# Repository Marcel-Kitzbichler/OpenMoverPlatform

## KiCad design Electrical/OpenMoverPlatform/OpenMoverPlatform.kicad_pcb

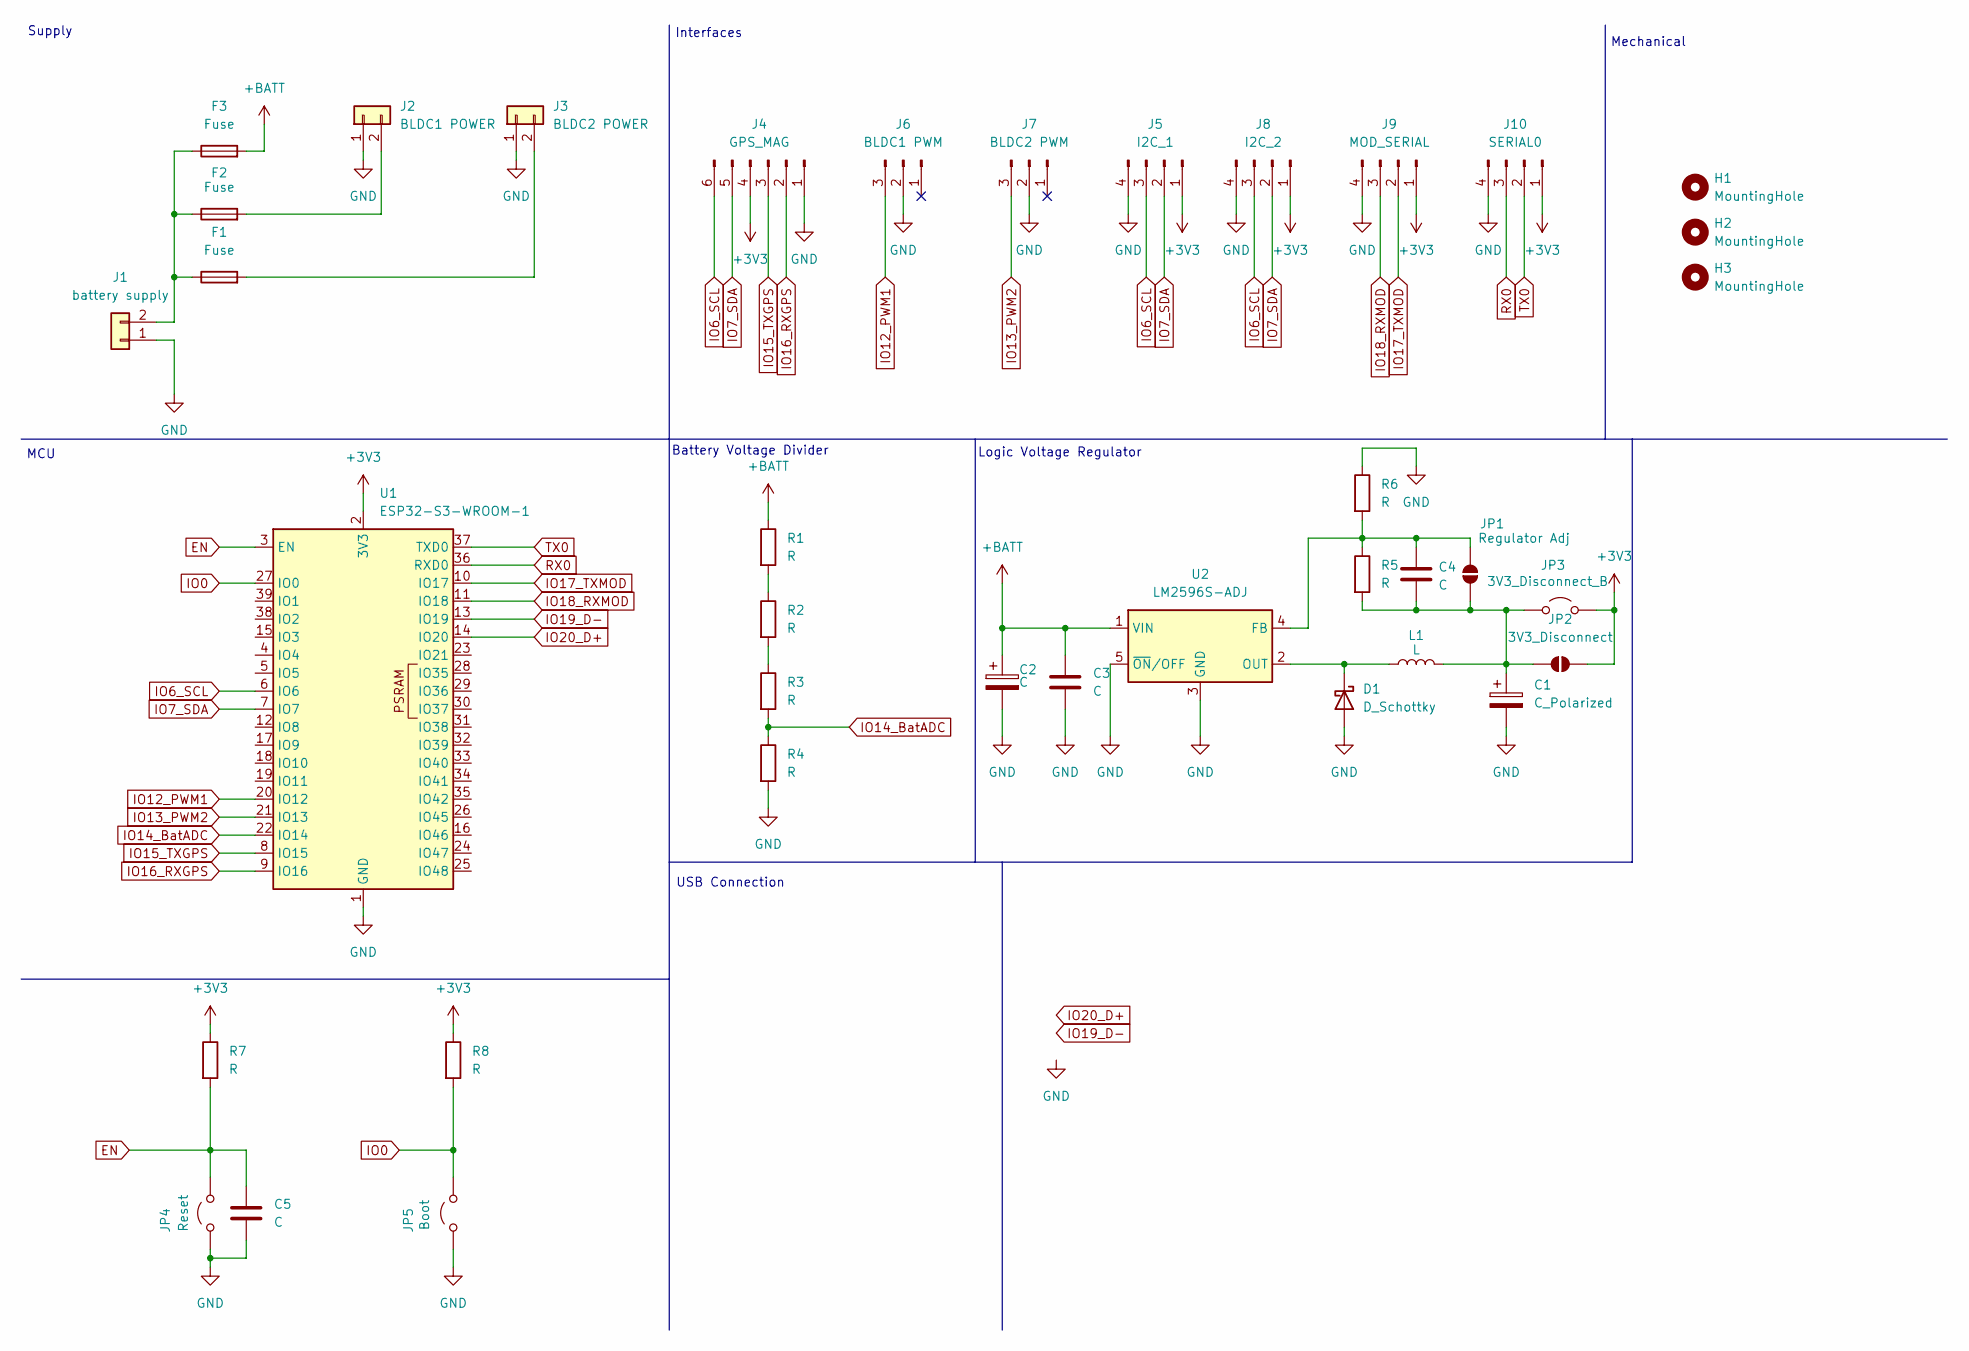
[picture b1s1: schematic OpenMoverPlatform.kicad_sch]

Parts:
C1: C_Polarized; CP_Elec_8x10.5
C2: C; CP_Elec_8x10.5
C3, C4, C5: C; C_1210_3225Metric_Pad1.33x2.70mm_HandSolder
D1: D_Schottky; D_SMA-SMB_Universal_Handsoldering
F1, F2, F3: Fuse; Fuseholder_Blade_Mini_Keystone_3568
H1, H2, H3: MountingHole; MountingHole_3.2mm_M3
J1: battery supply; AMASS_XT60-M_1x02_P7.20mm_Vertical
J2: BLDC1 POWER; AMASS_XT60-F_1x02_P7.20mm_Vertical
J3: BLDC2 POWER; AMASS_XT60-F_1x02_P7.20mm_Vertical
J4: GPS_MAG; PinHeader_1x06_P2.54mm_Vertical
J5: I2C_1; PinHeader_1x04_P2.54mm_Vertical
J6: BLDC1 PWM; PinHeader_1x03_P2.54mm_Vertical
J7: BLDC2 PWM; PinHeader_1x03_P2.54mm_Vertical
J8: I2C_2; PinHeader_1x04_P2.54mm_Vertical
J9: MOD_SERIAL; PinHeader_1x04_P2.54mm_Vertical
J10: SERIAL0; PinHeader_1x04_P2.54mm_Vertical
JP1: Regulator Adj; SolderJumper-2_P1.3mm_Open_TrianglePad1.0x1.5mm
JP2: 3V3_Disconnect; SolderJumper-2_P1.3mm_Open_TrianglePad1.0x1.5mm
JP3: 3V3_Disconnect_B; PinHeader_2x01_P2.54mm_Vertical
JP4: Reset; PinHeader_2x01_P2.54mm_Vertical
JP5: Boot; PinHeader_2x01_P2.54mm_Vertical
L1: L; L_Bourns_SRR1260
R1, R2, R3, R4, R5, R6, R7, R8: R; R_1206_3216Metric_Pad1.30x1.75mm_HandSolder
U1: ESP32-S3-WROOM-1
U2: LM2596S-ADJ; TO-263-5_TabPin3

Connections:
+3V3: J4.4, J5.1, J8.1, J9.1, J10.1, JP2.2 (B), JP3.2 (B), R7.1, R8.1, U1.2 (3V3); also elsewhere on the board
+BATT: C2.1, C3.1, F3.2, R1.1, U2.1 (VIN)
EN: C5.1, JP4.2 (B), R7.2, U1.3 (EN)
GND: C1.2, C2.2, C3.2, C5.2, D1.2 (A), J1.1, J2.1, J3.1, J4.1, J5.4, J6.2, J7.2, J8.4, J9.4, J10.4, JP4.1 (A), JP5.1 (A), R4.2, R6.1, U1.1 (GND), U1.40 (GND), U1.41 (GND), U2.3 (GND), U2.5 (~ON/OFF); also elsewhere on the board
IO0: JP5.2 (B), R8.2, U1.27 (IO0)
IO6_SCL: J4.6, J5.3, J8.3, U1.6 (IO6)
IO7_SDA: J4.5, J5.2, J8.2, U1.7 (IO7)
IO12_PWM1: J6.3, U1.20 (IO12)
IO13_PWM2: J7.3, U1.21 (IO13)
IO14_BatADC: R3.2, R4.1, U1.22 (IO14)
IO15_TXGPS: J4.3, U1.8 (IO15)
IO16_RXGPS: J4.2, U1.9 (IO16)
IO17_TXMOD: J9.2, U1.10 (IO17)
IO18_RXMOD: J9.3, U1.11 (IO18)
IO19_D-: U1.13 (IO19); also elsewhere on the board
IO20_D+: U1.14 (IO20); also elsewhere on the board
unnamed: D1.1 (K), L1.1, U2.2 (OUT)
unnamed: F1.1, F2.1, F3.1, J1.2
unnamed: F2.2, J2.2
unnamed: F1.2, J3.2
unnamed: C1.1, C4.2, JP1.1 (A), JP2.1 (A), JP3.1 (A), L1.2, R5.2
unnamed: C4.1, JP1.2 (B), R5.1, R6.2, U2.4 (FB)
unnamed: R1.2, R2.1
unnamed: R2.2, R3.1
RX0: J10.3, U1.36 (RXD0)
TX0: J10.2, U1.37 (TXD0)

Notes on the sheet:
Supply
Battery Voltage Divider
USB Connection
Mechanical
MCU
Logic Voltage Regulator
Interfaces

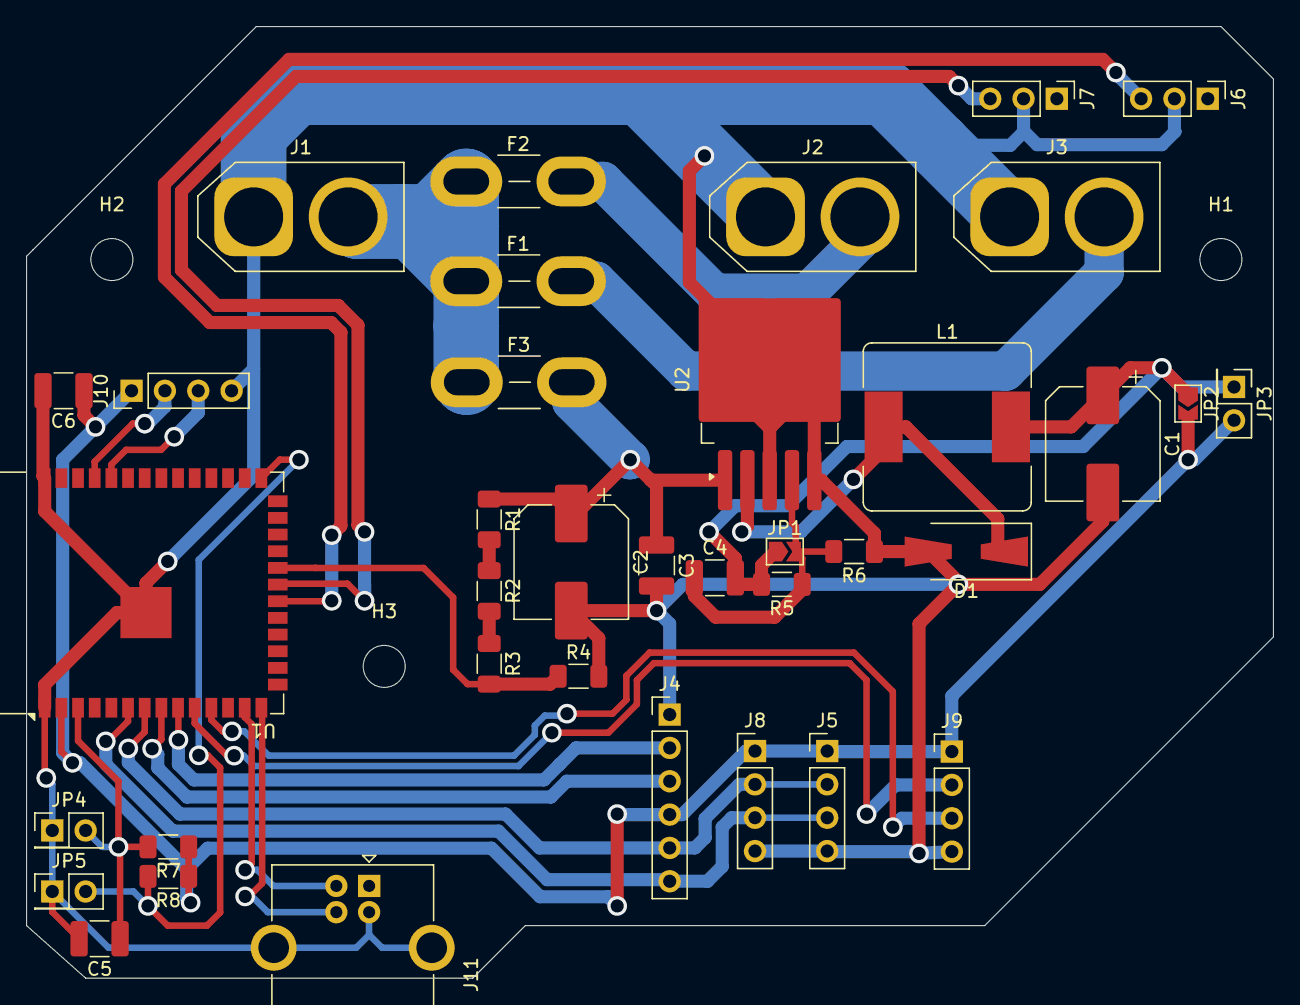
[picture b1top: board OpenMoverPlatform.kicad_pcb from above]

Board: 2 copper layers, 95.0 x 72.5 mm, 40 parts (0 on the bottom side), 26 nets.

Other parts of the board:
C6: C; C_1210_3225Metric_Pad1.33x2.70mm_HandSolder
J11: USB_B; USB_B_OST_USB-B1HSxx_Horizontal

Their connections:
+3V3: C6.1; also elsewhere on the board
GND: C6.2, J11.4 (GND), J11.5 (Shield); also elsewhere on the board
IO19_D-: J11.2 (D-); also elsewhere on the board
IO20_D+: J11.3 (D+); also elsewhere on the board

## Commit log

2024-11-12 added kicad project
2024-11-12 created platformcode
2024-11-12 KiCad save
2024-11-14 Rough sketch of chassis
    Not really to scale
2024-11-14 added DRIVEUNIT_V1
2024-11-15 update meshes
2024-11-15 updated motor mount
2024-11-21 added v2 driveunit
2024-11-29 swx update
2024-11-29 create platform io project
2024-12-06 Platform basic communication
2024-12-06 added coordinate parsing
2024-12-09 platfom update
2024-12-10 code update
2024-12-10 Passing data to WP manager
2024-12-12 added helper
2024-12-12 rearranged main
2024-12-12 added elif tree
2024-12-12 added example data
2024-12-12 added motor instance checking
2024-12-13 added multiple files to bot helper
2024-12-13 Changed intent numbering
2025-01-16 chain
    Added added chain design from filzer and set it to the correct length
2025-01-20 worked on coordinate storage
2025-01-20 added kml parser
2025-01-20 added coordinate transmission to helper
2025-01-20 added kml sample
2025-01-21 fixed PWM
2025-01-22 pwmUpdate
2025-01-22 updated deprecated json datatypes
2025-01-27 made usecPWM const
2025-01-27 added gps config
2025-01-28 removed debug messages
2025-01-28 added gps debug
2025-02-27 swxUpdate
2025-04-15 added bluetooth serial
2025-04-16 added direct serial control
2025-04-16 added Battery Reading Intent 6
2025-04-16 updated serial Timing and fixed correct decimal
2025-04-22 added motor set
2025-04-23 updated parsekml
2025-04-24 better gps
2025-04-24 update emerg
2025-04-30 added goto
2025-05-01 goto with compass
2025-05-02 updated bot helper
2025-05-06 Rim to WheelHolder
    Added a chain guide rail to make sure the chain doesn't slip off.
2025-05-08 added WP Manager and compass calibration routines
2025-05-08 updated bot helper desktop application
2025-05-08 added preferences with mag not yet implemented and intent 10
2025-05-10 Connector tolerance
    Updated connector tolerances to improve fit.
2025-05-12 corrected data type saved by preferences
2025-05-13 added nonlinear stearing curve
2025-05-13 added setpoints to motorset
2025-05-13 added setpoint to status
2025-05-14 control pcb v1
2025-05-16 ki cad pcb update
2025-05-16 added esp32s3 environment
2025-05-18 updated pcb to use esp32 s3 wroom 1
2025-05-29 working com on esp devboard, untested hardware peripherals
2025-05-29 add to last commit
2025-05-30 BLE Serial end detection
2025-05-30 updated to new ledc api
2025-10-23 update 2025
2025-11-27 helper update
2025-11-27 ini update
2025-12-10 Initial plan
2025-12-10 Add enhanced CLI and modern GUI for platform helper tool
2025-12-10 Add comprehensive documentation and usage examples
2025-12-10 Fix code review issues: integer division and type-safe formatting
2025-12-10 Add changelog documenting all enhancements
2025-12-10 small fix
2026-01-20 wokwi update
2026-01-20 added helper net serial
2026-01-28 doc begin
2026-01-29 Doc Halbjahr
2026-02-19 fixed some deprecated code
